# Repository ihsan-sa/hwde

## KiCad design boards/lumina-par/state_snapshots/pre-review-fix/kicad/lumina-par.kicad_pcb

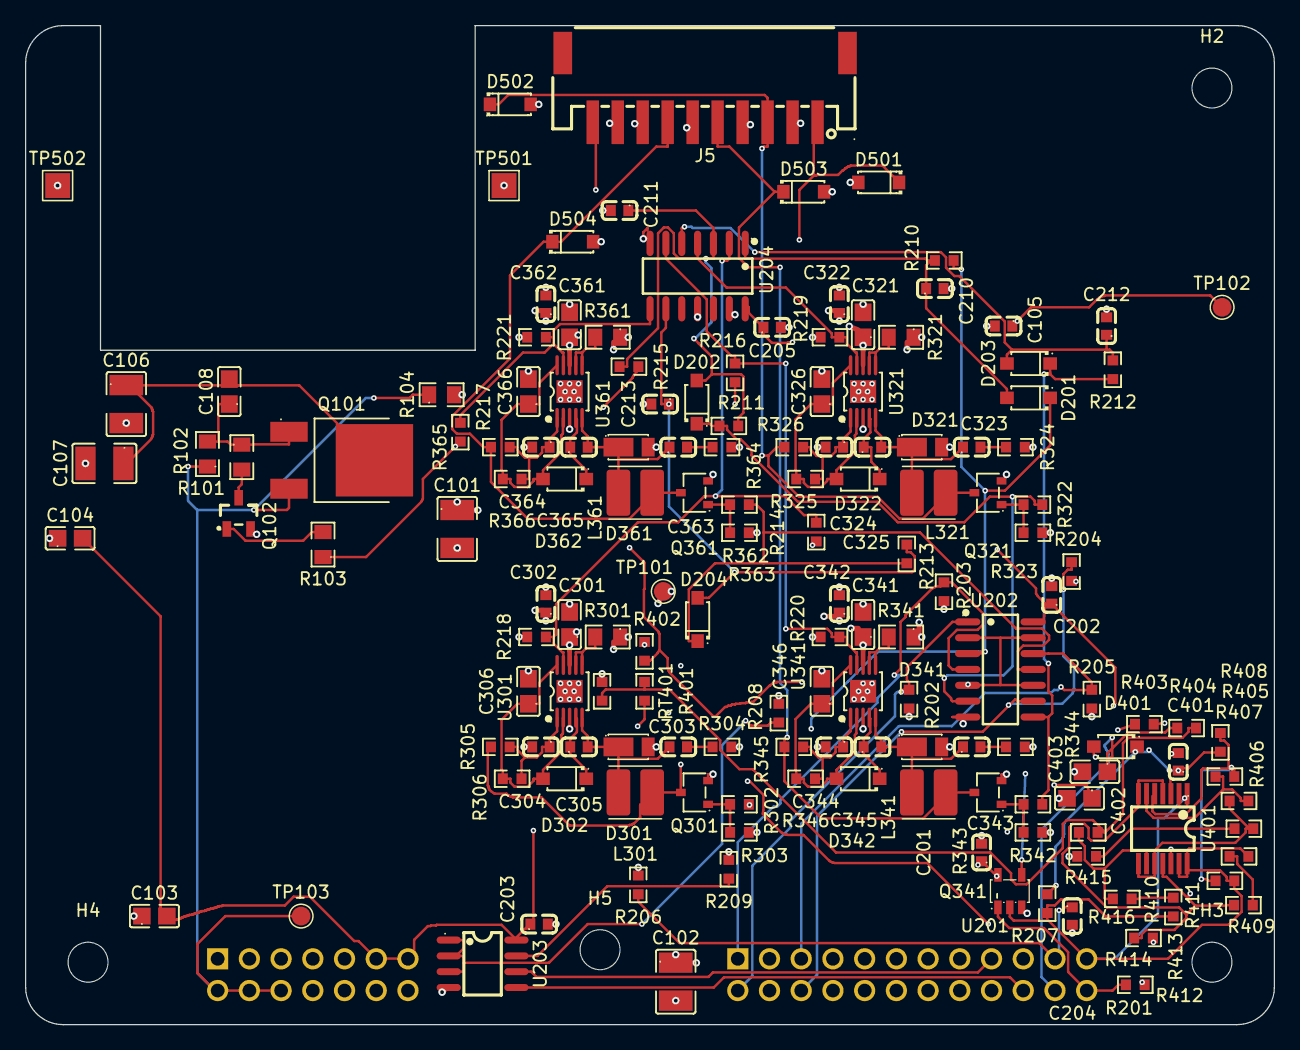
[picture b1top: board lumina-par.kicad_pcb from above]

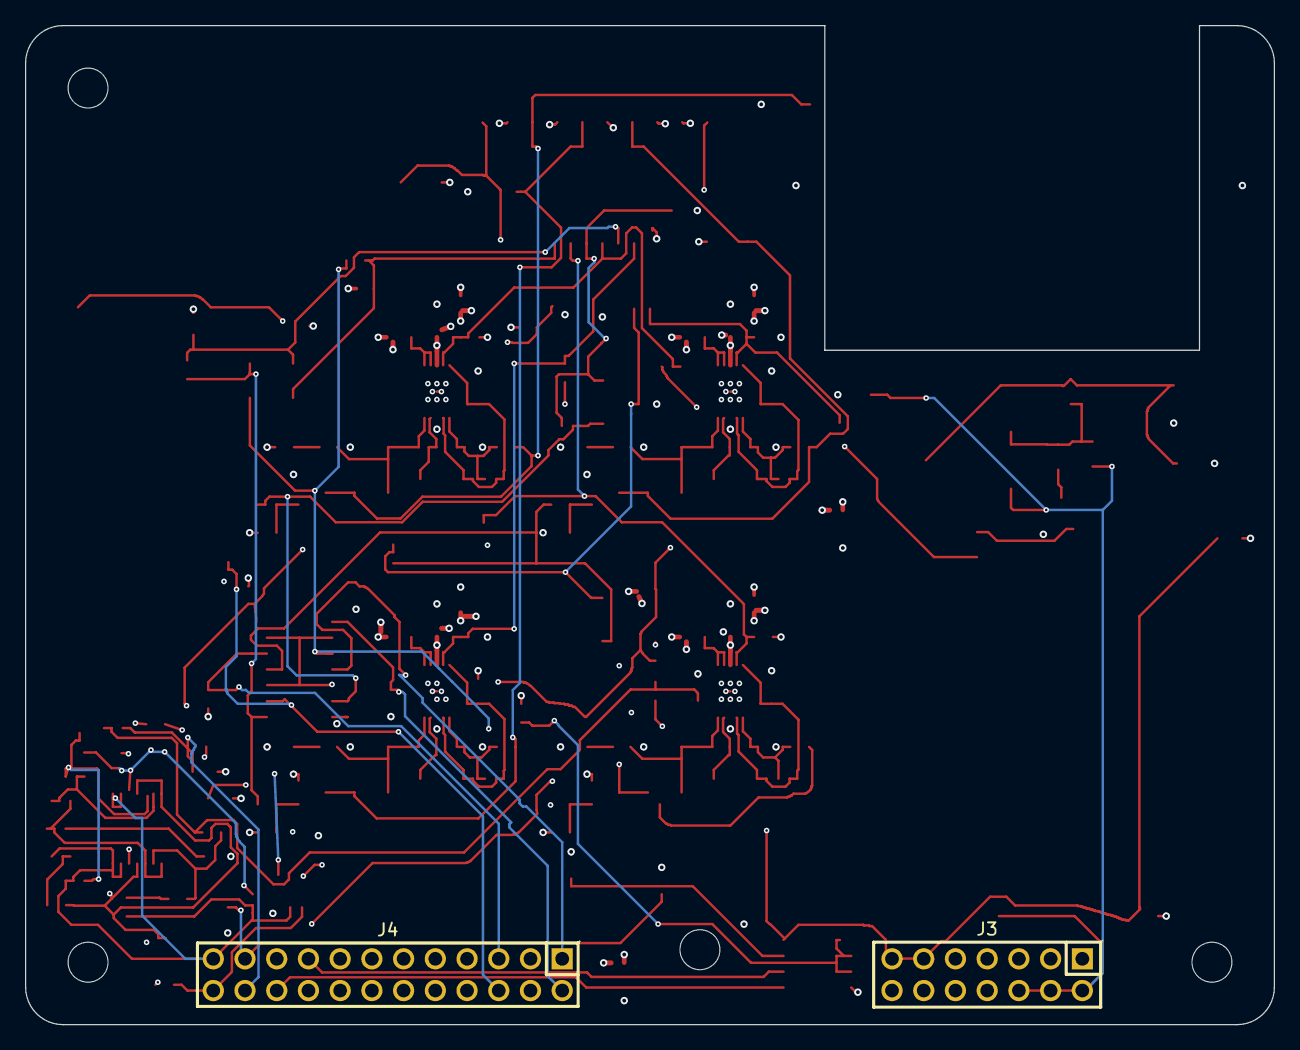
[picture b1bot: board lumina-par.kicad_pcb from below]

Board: 4 copper layers, 100.0 x 80.0 mm, 158 parts (2 on the bottom side), 76 nets.

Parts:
C101, C102: 22uF 25V X7R 1210; C1210
C103, C104: 10uF 16V X7R 0805; C0805
C105, C201, C202, C203, C204, C205, C302, C305, C322, C325, C342, C345, C362, C365, C401: 100nF 50V X7R 0603; C0603
C106, C107: 10uF 100V X7R 1210; C1210
C108: 33nF 100V X7R 0805; C0805
C210, C211, C212, C213: 10nF 50V X7R 0603; C0603
C301, C306, C321, C326, C341, C346, C361, C366, C402, C403: 4.7uF 25V X7R 0805; C0805
C303, C323, C343, C363: 1nF 100V X7R 0603; C0603
C304, C324, C344, C364: 470pF 50V C0G 0603; C0603
D201, D202, D203, D204, D401: 1N4148W switching diode, SOD-123; SOD-123F_L2.7-W1.6-LS3.8-RD
D301, D321, D341, D361: DFLS160-7 60V 1A Schottky; POWERDI-123_L2.8-W1.8-LS3.7-RD
D302, D322, D342, D362: 1N4148W 100V fast switching; SOD-123F_L2.7-W1.6-LS3.8-RD
D501, D502, D503, D504: SMF15A 15V unidirectional TVS, SOD-123; SOD-123_L2.7-W1.8-LS3.7-RD
H2, H3, H4, H5: MountingHole_3.2mm_M3
J3: DS1023-2*7SF11 2x7 socket 2.54mm 600V; HDR-TH_14P-P2.54-V-F-R2-C7-S2.54-1
J4: DS1023-2*12SF11 2x12 socket, 2.54 mm, 600 V, 3 A/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; HDR-TH_24P-P2.54-V-F-R2-C12-S2.54
J5: S10B-PH-SM4-TB JST PH 10-way SMD header, 2.0 mm; CONN-SMD_S10B-PH-SM4-TB-LF-SN
L301, L321, L341, L361: 47uH shielded 950mA; L_Cenker_CKCS4030
Q101: NCE01P13K -100V P-MOSFET TO-252; TO-252-2_L6.6-W6.1-P4.57-LS10.1-TL-CW
Q102: BSS123 100V N-MOSFET SOT-23; SOT-23-3_L2.9-W1.5-P1.90-LS2.6-BR
Q301, Q321, Q341, Q361: SSM3K2615R 60V 2A N-FET; SOT-23F_L2.9-W1.8-P1.90-LS2.4-BR
R101, R104: 100k 0805 1%; R0805
R102, R103: 10k 0805 1%; R0805
R201, R202, R203, R204, R205, R207, R210, R211, R212, R213, R409, R411, R412, R414: 100k 0603 1%; R0603
R206: 4.7k 0603 1%; R0603
R208, R214, R215, R216, R217: 0R 0603; R0603
R209, R218, R219, R220, R221, R401, R403, R410, R413, R415: 10k 0603 1%; R0603
R301, R321, R341, R361: 0.75R 1% 0805; R0805
R302, R322, R342, R362: 150R 1% 0603; R0603
R303, R323, R343, R363: 100k 1% 0603; R0603
R304, R324, R344, R364: 10R 0603; R0603
R305, R325, R345, R365: 10k 1% 0603; R0603
R306, R326, R346, R366: 30k 1% 0603; R0603
R402, R404: 150R 0603 1%; R0603
R405: 2.7k 0603 1%; R0603
R406: 27k 0603 1%; R0603
R407: 1.2k 0603 1%; R0603
R408, R416: 1.6k 0603 1%; R0603
RT401: 10k B3950 +-1% NTC 0603; R0603
TP101, TP102, TP103: TestPoint; TestPoint_Pad_D1.5mm
TP501, TP502: thermocouple pad, bare Cu; TestPoint_Pad_2.0x2.0mm
U201: SN74LVC1G08DBVR single 2-input AND, SOT-23-5; SOT-23-5_L3.0-W1.7-P0.95-LS2.8-BR
U202: SN74LVC00ADR quad 2-input NAND, SOIC-14; SOIC-14_L8.7-W3.9-P1.27-LS6.0-BL
U203: M24C32-WMN6TP 32 kbit I2C EEPROM, SOIC-8; SOIC-8_L5.0-W4.0-P1.27-LS6.0-BL
U204: SN74LVC14ADR hex Schmitt-trigger inverter, SOIC-14; SOIC-14_L8.7-W3.9-P1.27-LS6.0-BL
U301, U321, U341, U361: TPS92515HVDGQR; MSOP-10_L3.0-W3.0-P0.50-LS5.0-BL-EP
U401: LM339LVPWR quad open-drain comparator TSSOP-14; TSSOP-14_L5.0-W4.4-P0.65-LS6.4-BL

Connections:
+3V3: C103.2, C104.2, C105.1, C201.1, C202.1, C203.1, C205.1, C401.1, D401.1, J3.11, J3.13, R207.2, R401.1, R403.1, R405.1, TP102.1, U201.5, U202.14, U203.8, U204.14, U401.3
+12V: C101.1, C102.1, C301.1, C302.1, C321.1, C322.1, C341.1, C342.1, C361.1, C362.1, J3.10, J3.12, R301.1, R321.1, R341.1, R361.1, TP101.1, U301.8, U321.8, U341.8, U361.8
+48V_SW: J3.2, J3.4, J3.6, Q101.3, R101.1, R104.1, TP103.1
/ADC0: C402.1, J4.19, R402.2
/ADC1: C403.1, J4.22, R404.2
/DRV_EN0: R214.2, R218.1, U204.2, U301.9
/DRV_EN1: R215.2, R219.1, U204.4, U321.9
/DRV_EN2: R216.2, R220.1, U204.6, U341.9
/DRV_EN3: R217.2, R221.1, U204.8, U361.9
/EN_OK: R103.1, R214.1, R215.1, R216.1, R217.1, U201.4, U202.2, U202.5, U202.10, U202.13
/FAULT: J4.23, R207.1, R409.1, R410.1, R412.1, U201.2, U401.1, U401.2, U401.13, U401.14
/LED0_A: D501.1, J5.1, L301.2, Q301.3, R305.1
/LED1_A: D502.1, J5.3, L321.2, Q321.3, R325.1
/LED2_A: D503.1, J5.5, L341.2, Q341.3, R345.1
/LED3_A: D504.1, J5.7, L361.2, Q361.3, R365.1
/NTC_LED: J5.10, R402.1, R403.2, R413.1
/SHUNT0: D201.1, R210.1, R302.1, U202.3
/SHUNT1: D202.1, R211.1, R322.1, U202.6
/SHUNT2: D203.1, R212.1, R342.1, U202.8
/SHUNT3: D204.1, R213.1, R362.1, U202.11
/control/EE_ADDR: R208.1, U203.1, U203.2, U203.3
/control/EE_WC: R209.1, U203.7
/control/ENABLE: J4.24, R201.1, U201.1
/control/I2C_SCL: J4.17, U203.6
/control/I2C_SDA: J4.20, U203.5
/control/IDLE0: C210.1, D201.2, R210.2, U204.1
/control/IDLE1: C211.1, D202.2, R211.2, U204.3
/control/IDLE2: C212.1, D203.2, R212.2, U204.5
/control/IDLE3: C213.1, D204.2, R213.2, U204.9
/control/ID_ADC: C204.1, J4.21, R206.1
/control/PWM0: J4.2, R202.1, U202.1
/control/PWM1: J4.1, R203.1, U202.4
/control/PWM2: J4.6, R204.1, U202.9
/control/PWM3: J4.5, R205.1, U202.12
/drivers/BOOT0: C305.1, D302.1, U301.4
/drivers/BOOT1: C325.1, D322.1, U321.4
/drivers/BOOT2: C345.1, D342.1, U341.4
/drivers/BOOT3: C365.1, D362.1, U361.4
/drivers/COFF0: C304.1, R305.2, R306.2, U301.1
/drivers/COFF1: C324.1, R325.2, R326.2, U321.1
/drivers/COFF2: C344.1, R345.2, R346.2, U341.1
/drivers/COFF3: C364.1, R365.2, R366.2, U361.1
/drivers/CSN0: R301.2, U301.6, U301.7
/drivers/CSN1: R321.2, U321.6, U321.7
/drivers/CSN2: R341.2, U341.6, U341.7
/drivers/CSN3: R361.2, U361.6, U361.7
/drivers/SHG0: Q301.1, R302.2, R303.1
/drivers/SHG1: Q321.1, R322.2, R323.1
/drivers/SHG2: Q341.1, R342.2, R343.1
/drivers/SHG3: Q361.1, R362.2, R363.1
/drivers/SNUB0: C303.2, R304.1
/drivers/SNUB1: C323.2, R324.1
/drivers/SNUB2: C343.2, R344.1
/drivers/SNUB3: C363.2, R364.1
/drivers/SW0: C303.1, C305.2, D301.1, L301.1, U301.5
/drivers/SW1: C323.1, C325.2, D321.1, L321.1, U321.5
/drivers/SW2: C343.1, C345.2, D341.1, L341.1, U341.5
/drivers/SW3: C363.1, C365.2, D361.1, L361.1, U361.5
/drivers/VCC0: C306.1, D302.2, R306.1, U301.2, U301.10
/drivers/VCC1: C326.1, D322.2, R326.1, U321.2, U321.10
/drivers/VCC2: C346.1, D342.2, R346.1, U341.2, U341.10
/drivers/VCC3: C366.1, D362.2, R366.1, U361.2, U361.10
/power/Q101_G: C108.1, Q101.1, R101.2, R102.1
/power/Q102_D: Q102.3, R102.2
/power/Q102_G: Q102.1, R103.2
/power/V48_B: C106.1, C107.1, C108.2, Q101.2
/thermal/CMP_BRD: R414.2, R415.2, U401.9
/thermal/CMP_LED: D401.2, R411.2, R413.2, U401.4, U401.7, U401.11
/thermal/HYS_BRD: R412.2, R414.1
/thermal/HYS_LED: R409.2, R411.1
/thermal/LAD_D: R408.2, R416.1
/thermal/NTC_BRD: R401.2, R404.1, R415.1, RT401.1
/thermal/VREF_EHOT: R406.2, R407.1, U401.6
/thermal/VREF_HOT2: R407.2, R408.1, U401.8, U401.10
/thermal/VREF_OPEN: R405.2, R406.1, R410.2, U401.5
GND: C101.2, C102.2, C103.1, C104.1, C105.2, C106.2, C107.2, C201.2, C202.2, C203.2, C204.2, C205.2, C210.2, C211.2, C212.2, C213.2, C301.2, C302.2, C304.2, C306.2, C321.2, C322.2, C324.2, C326.2, C341.2, C342.2, C344.2, C346.2, C361.2, C362.2, C364.2, C366.2, C401.2, C402.2, C403.2, D301.2, D321.2, D341.2, D361.2, D501.2, D502.2, D503.2, D504.2, J3.1, J3.3, J3.5, J3.7, J3.8, J3.9, J3.14, J4.3, J4.4, J4.9, J4.10, J4.14, J5.2, J5.4, J5.6, J5.8, J5.9, Q102.2, Q301.2, Q321.2, Q341.2, Q361.2, R104.2, R201.2, R202.2, R203.2, R204.2, R205.2, R206.2, R208.2, R209.2, R218.2, R219.2, R220.2, R221.2, R303.2, R304.2, R323.2, R324.2, R343.2, R344.2, R363.2, R364.2, R416.2, RT401.2, TP501.1, TP502.1, U201.3, U202.7, U203.4, U204.7, U204.11, U204.13, U301.3, U301.11, U321.3, U321.11, U341.3, U341.11, U361.3, U361.11, U401.12

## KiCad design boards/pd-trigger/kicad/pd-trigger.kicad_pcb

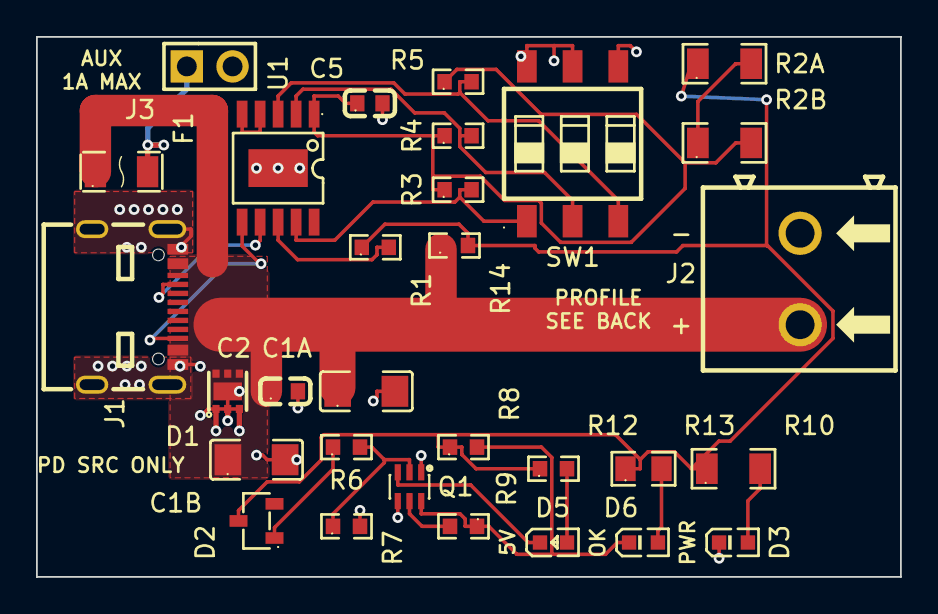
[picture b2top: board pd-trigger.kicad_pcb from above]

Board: 2 copper layers, 48.0 x 30.0 mm, 30 parts (0 on the bottom side), 21 nets.

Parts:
C1A, C1B: 10uF 50V X5R; C1206
C2: 100nF 50V X7R; C0603
C5: 1uF 50V X5R; C0603
D1: TVS2200 22V; WSON-6_L2.0-W2.0-P0.65-BL-EP
D2: BZX84C6V2; SOT-23-3_L2.9-W1.3-P1.90-LS2.4-BR
D3: LED YG PWR; LED0603-RD_GREEN
D5: LED RED 5V ONLY; LED0603-RD
D6: LED YG PROFILE OK; LED0603-RD_GREEN
F1: PPTC 1A 30V; F1206
J1: USB-C 16P 5A; USB-C-SMD_MC-311D
J2: SCREW 5.08 2P; CONN-TH_P5.08_KF128-5.08-2P
J3: HDR 1x2 AUX; HDR-TH_2P-P2.54-V-M-3
Q1: BC847BS; SOT-363-6_L2.2-W1.3-P0.65-LS2.1-BL
R1, R8: 10k; R0603
R2A, R2B: 510R; R1206
R3, R4, R5: 100k; R0603
R6: 6.8k; R0603
R7: 4.7k; R0603
R9: 47k; R0603
R10: 3.3k; R1206
R12: 1.5k; R0603
R13: 4.7k; R0805
R14: 0R; R0603
SW1: DIP-3; SW-SMD_6P-L7.6-W6.0-P2.54-LS9.3-BL
U1: CH224K; ESSOP-10_L4.9-W3.9-P1.0-LS6.0-TL-EP

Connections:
/BC12_DIS: U1.4, U1.5
/CC1: J1.A5, U1.7
/CC2: J1.B5, U1.6
/CFG1: R3.2, SW1.1, U1.9
/CFG2: R4.2, SW1.2, U1.2
/CFG3: R5.2, SW1.3, U1.3
/D3_A: D3.2, R10.2
/D5_A: D5.2, R12.2
/D6_A: D6.2, R13.2
/FB_B: Q1.5, R9.2
/FB_K: D5.1, Q1.3
/HV_B: Q1.2, R6.2, R7.1
/HV_OK: D6.1, Q1.6, R8.2, R9.1
/R2_MID: R2A.2, R2B.1
/VAUX: F1.2, J3.1
/VDD: C5.1, R2B.2, R3.1, R4.1, R5.1, U1.1
/VIND: D2.3, R1.1, R2A.1, R8.1, R10.1, R12.1, R13.1, R14.2
/VSENSE: R1.2, U1.8
/ZBIAS: D2.1, R6.1
GND: C1A.2, C1B.2, C2.2, C5.2, D1.1, D1.2, D1.3, D1.7, D3.1, J1.1, J1.2, J1.3, J1.4, J1.A1-B12, J1.B1-A12, J2.2, J3.2, Q1.1, Q1.4, R7.2, SW1.4, SW1.5, SW1.6, U1.11
VBUS: C1A.1, C1B.1, C2.1, D1.4, D1.5, D1.6, F1.1, J1.A4-B9, J1.B4-A9, J2.1, R14.1

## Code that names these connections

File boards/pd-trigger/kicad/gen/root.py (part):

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functional chain, every block-crossing net is a rail or a two-part stub, and
the only multi-block signal (/HV_OK) lives inside the indication fan-out.
Consequence: all local labels are root-local, so they appear in the netlist
as `/NAME` - which is exactly what constraints.json declares for /VAUX,
/VIND and /VDD. VBUS and GND are power SYMBOLS, hence bare.

WIRING FACTS - ground truth, not memory
---------------------------------------
U1 CH224K (parts/C970725.json, WCH manual V2.1 tables 4-2 / 6.2 / 7.1 /
8.1.3 / 8.2.3; pad numbering re-confirmed in reports/lib_verify.json):
  pins 1 VDD, 2 CFG2, 3 CFG3, 4 DP, 5 DM, 6 CC2, 7 CC1, 8 VBUS(sense),
  9 CFG1, 10 PG, and GND = **pad 11** - the datasheet calls the exposed
  baseplate "pin 0" and it is the part's ONLY ground terminal; the pulled
  symbol AND footprint both number it 11 (V11 resolved: they agree).
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Topology (blocks.md B1-B6, decisions.md D1-D7 + A1):
  VBUS is ONE copper object end to end - receptacle, TVS, bulk, both taps
  and the screw terminal. There is no VOUT and no series element in the 5 A
  path. /VIND is VBUS behind the 0 ohm link R14 and feeds ALL housekeeping
  (R1 sense, R2A/R2B dropper, the D2 window bias, R8, and the three LED
  legs) so check_current does not force 1.75 mm copper onto every stub.
  /VAUX is its own net behind the PPTC F1.
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Deviations from the assignment brief, resolved in favour of the authorities
(architecture/blocks.md B2/B4/B5 + sheets.md s1 + parts/parts.json roles):
  - the dropper and the sense resistor hang off **/VIND**, not VBUS
    (sheets.md s1: "/VIND | R14 pin 2, R1, R2, R6, R8, R10, R12, R13").
  - the 10 k VBUS-sense resistor is **R1**; **R6** is the 6.8 k window base
    resistor. The brief swapped the two refdes.
  - the window detector is the full blocks.md B5 network: D2 + R6 into
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    # is negotiated and the source stays at its 5 V default.
    sh.add_component(S_R_0R, "R14", "0R", at=(190.5, 60.96),
                     footprint=F_R0603)
    sh.wire_pins("R14", {"1": "VBUS", "2": "VIND"})

    # ======================================================== B6 output + aux
    sh.add_component(S_J2, "J2", "SCREW 5.08 2P", at=(241.3, 88.9),
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    sh.wire_pins("J2", {"1": "VBUS", "2": "GND"})
    sh.add_component(S_F1, "F1", "PPTC 1A 30V", at=(241.3, 60.96),
                     footprint=f"{FP}:F1206")
    sh.wire_pins("F1", {"1": "VBUS", "2": "VAUX"})
    sh.add_component(S_J3, "J3", "HDR 1x2 AUX", at=(292.1, 60.96),
                     footprint=f"{FP}:HDR-TH_2P-P2.54-V-M-3")
    sh.wire_pins("J3", {"1": "VAUX", "2": "GND"})

    # ============================================ B2 controller + its supply
    # C5 is the datasheet's ONLY specified capacitor for this part (table
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    # R1: mandatory 10 k series into the VBUS-detect pin.
    sh.add_component(S_R_10K, "R1", "10k", at=(215.9, 165.1),
                     footprint=F_R0603)
    sh.wire_pins("R1", {"1": "VIND", "2": "VSENSE"})
    # R2A + R2B: the datasheet's dropper, shipped as 2x 510 R 1206 in series
    # (~1020 R) because no Basic-tier 1 k 2512 exists - 0.157 W each at 21 V
    # against 0.25 W parts. The single-package 1 k 2512 burning 0.31 W is the
    # architecture's primary; this is its pre-approved alternate (A1.3).
    sh.add_component(S_R_510, "R2A", "510R", at=(215.9, 180.34),
                     footprint=F_R1206)
    sh.wire_pins("R2A", {"1": "VIND", "2": "R2_MID"})
    sh.add_component(S_R_510, "R2B", "510R", at=(215.9, 195.58),
                     footprint=F_R1206)
    sh.wire_pins("R2B", {"1": "R2_MID", "2": "VDD"})

    # ======================================================= B3 profile select
    # 100 k (not 10 k) to /VDD: at the 5 V profile the whole /VDD node is fed
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                     footprint=f"{FP}:SW-SMD_6P-L7.6-W6.0-P2.54-LS9.3-BL",
                     expect={"1": "A1", "2": "A2", "3": "A3", "4": "A4",
                             "5": "A5", "6": "A6"})
    sh.wire_pins("SW1", {"1": "CFG1", "6": "GND",     # pole 1
                         "2": "CFG2", "5": "GND",     # pole 2
                         "3": "CFG3", "4": "GND"})    # pole 3

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    # hence 1206).
    sh.add_component(S_R_3K3, "R10", "3.3k", at=(76.2, 190.5),
                     footprint=F_R1206)
    sh.wire_pins("R10", {"1": "VIND", "2": "D3_A"})
    sh.add_component(S_LED_YG, "D3", "LED YG PWR", at=(114.3, 190.5),
                     footprint=F_LED_YG, expect={"1": "K", "2": "A"})
    sh.wire_pins("D3", {"2": "D3_A", "1": "GND"})

    # Window detector: D2 (6.2 V zener, cathode on /VIND) + R6 6k8 into
    # Q1A's base, R7 4k7 base-emitter shunt so zener knee leakage at 5.25 V
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    sh.add_component(S_D2, "D2", "BZX84C6V2", at=(76.2, 228.6),
                     footprint=f"{FP}:SOT-23-3_L2.9-W1.3-P1.90-LS2.4-BR",
                     expect={"1": "A", "3": "K"})
    sh.wire_pins("D2", {"3": "VIND",    # cathode to the bus stub
                        "1": "ZBIAS",   # anode into the base chain
                        "2": "NC"})     # SOT-23 centre lead: no function
    sh.add_component(S_R_6K8, "R6", "6.8k", at=(114.3, 228.6),
                     footprint=F_R0603)
    sh.wire_pins("R6", {"1": "ZBIAS", "2": "HV_B"})
    sh.add_component(S_R_4K7, "R7", "4.7k", at=(114.3, 243.84),
                     footprint=F_R0603)
    sh.wire_pins("R7", {"1": "HV_B", "2": "GND"})

    # Q1A = TR1 (pins 2 B / 1 E / 6 C) is the comparator; Q1B = TR2
    # (5 B / 4 E / 3 C) inverts it, so exactly one of D5/D6 is ever lit.
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                     footprint=f"{FP}:SOT-363-6_L2.2-W1.3-P0.65-LS2.1-BL",
                     expect={"1": "E", "2": "B", "3": "C",
                             "4": "E", "5": "B", "6": "C"})
    sh.wire_pins("Q1", {"2": "HV_B", "1": "GND", "6": "HV_OK",    # Q1A
                        "5": "FB_B", "4": "GND", "3": "FB_K"})    # Q1B
    sh.add_component(S_R_10K, "R8", "10k", at=(215.9, 228.6),
                     footprint=F_R0603)
    sh.wire_pins("R8", {"1": "VIND", "2": "HV_OK"})
    sh.add_component(S_R_47K, "R9", "47k", at=(215.9, 243.84),
                     footprint=F_R0603)
    sh.wire_pins("R9", {"1": "HV_OK", "2": "FB_B"})

    # D5 "5V ONLY" (red) conducts ONLY below the 6.7 V trip, through Q1B;
    # D6 "PROFILE OK" (green) only above it, into Q1A's collector node. Each
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    # the scheme.
    sh.add_component(S_R_1K5, "R12", "1.5k", at=(76.2, 254.0),
                     footprint=F_R0603)
    sh.wire_pins("R12", {"1": "VIND", "2": "D5_A"})
    sh.add_component(S_LED_RD, "D5", "LED RED 5V ONLY", at=(114.3, 254.0),
                     footprint=F_LED_RD, expect={"1": "K", "2": "A"})
    sh.wire_pins("D5", {"2": "D5_A", "1": "FB_K"})
    sh.add_component(S_R_4K7_0805, "R13", "4.7k", at=(76.2, 269.24),
                     footprint=F_R0805)
    sh.wire_pins("R13", {"1": "VIND", "2": "D6_A"})
    sh.add_component(S_LED_YG, "D6", "LED YG PROFILE OK", at=(114.3, 269.24),
                     footprint=F_LED_YG, expect={"1": "K", "2": "A"})
    sh.wire_pins("D6", {"2": "D6_A", "1": "HV_OK"})

    # ================================================================== rails
    # VBUS and GND are power SYMBOLS (global, bare names). Every driver on
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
